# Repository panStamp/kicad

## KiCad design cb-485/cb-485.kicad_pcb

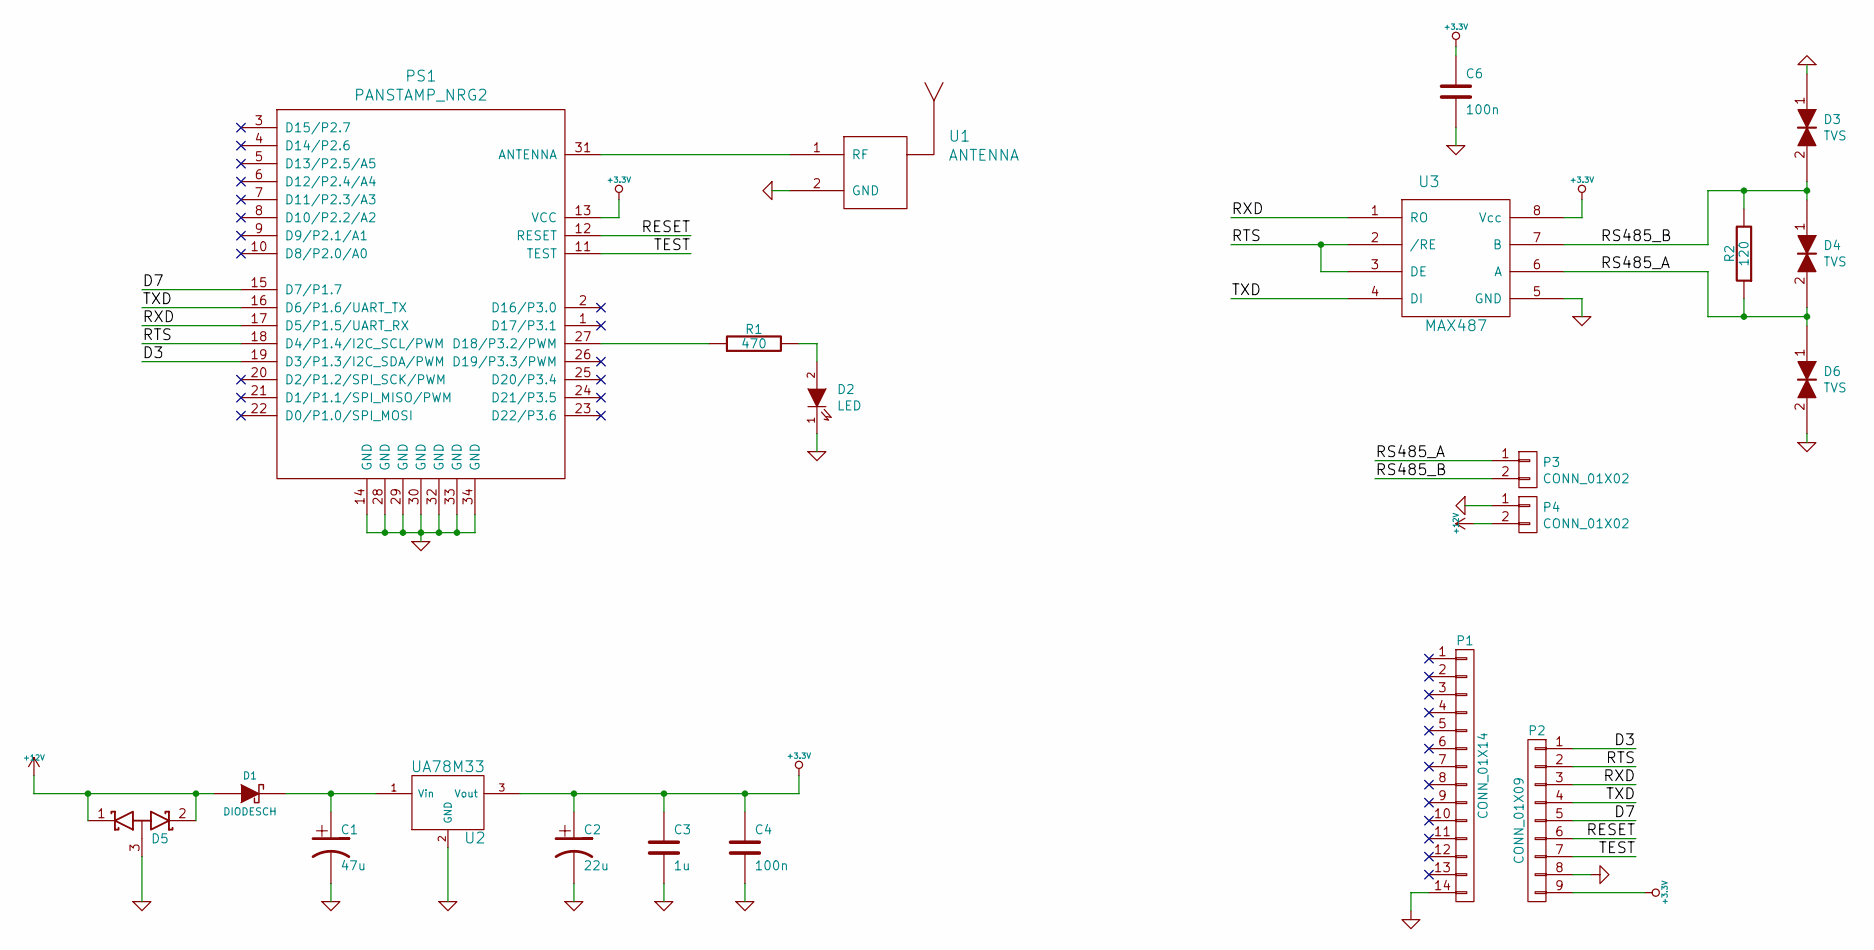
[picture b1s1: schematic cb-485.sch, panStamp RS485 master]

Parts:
C1: 47u; SMDCPOL_6.3
C2: 22u; SMDCPOL_5
C3: 1u; SM0603S
C4, C6: 100n; SM0603S
D1: DIODESCH; SMA
D2: LED; SM0603S_POL
D3, D4, D6: TVS; SOD-923
D5: D_Schottky_x2_ACom_KKA; SOT23
P1: CONN_01X14; Pin_Header_Straight_1x12
P2: CONN_01X09; Pin_Header_Straight_1x09
P3, P4: CONN_01X02; terminal_block_5mm_2P
PS1: PANSTAMP_NRG2; PANSTAMP_2
R1: 470; SM0603S
R2: 120; SM0603S
U1: ANTENNA; SMA_RightAngle_Tyco
U2: UA78M33; SOT223
U3: MAX487; SO8E

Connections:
+3.3V: C2.1, C3.1, C4.1, C6.1, P2.9, PS1.13 (VCC), U2.3 (Vout), U3.8 (Vcc)
+12V: D1.1 (A), D5.1 (K), D5.2 (K), P4.2
/D3: P2.1, PS1.19 (D3/P1.3/I2C_SDA/PWM)
/D7: P2.5, PS1.15 (D7/P1.7)
/RESET: P2.6, PS1.12 (RESET)
/RS485_A: D4.2, D6.1, P3.1, R2.1, U3.6 (A)
/RS485_B: D3.2, D4.1, P3.2, R2.2, U3.7 (B)
/RTS: P2.2, PS1.18 (D4/P1.4/I2C_SCL/PWM), U3.2 (/RE), U3.3 (DE)
/RXD: P2.3, PS1.17 (D5/P1.5/UART_RX), U3.1 (RO)
/TEST: P2.7, PS1.11 (TEST)
/TXD: P2.4, PS1.16 (D6/P1.6/UART_TX), U3.4 (DI)
GND: C1.2, C2.2, C3.2, C4.2, C6.2, D2.1 (K), D3.1, D5.3 (A), D6.2, P1.14, P2.8, P4.1, PS1.14 (GND), PS1.28 (GND), PS1.29 (GND), PS1.30 (GND), PS1.32 (GND), PS1.33 (GND), PS1.34 (GND), U1.2 (GND), U2.2 (GND), U2.4, U3.5 (GND)
unnamed: C1.1, D1.2 (K), U2.1 (Vin)
unnamed: D2.2 (A), R1.2
unnamed: PS1.27 (D18/P3.2/PWM), R1.1
unnamed: PS1.31 (ANTENNA), U1.1 (RF)

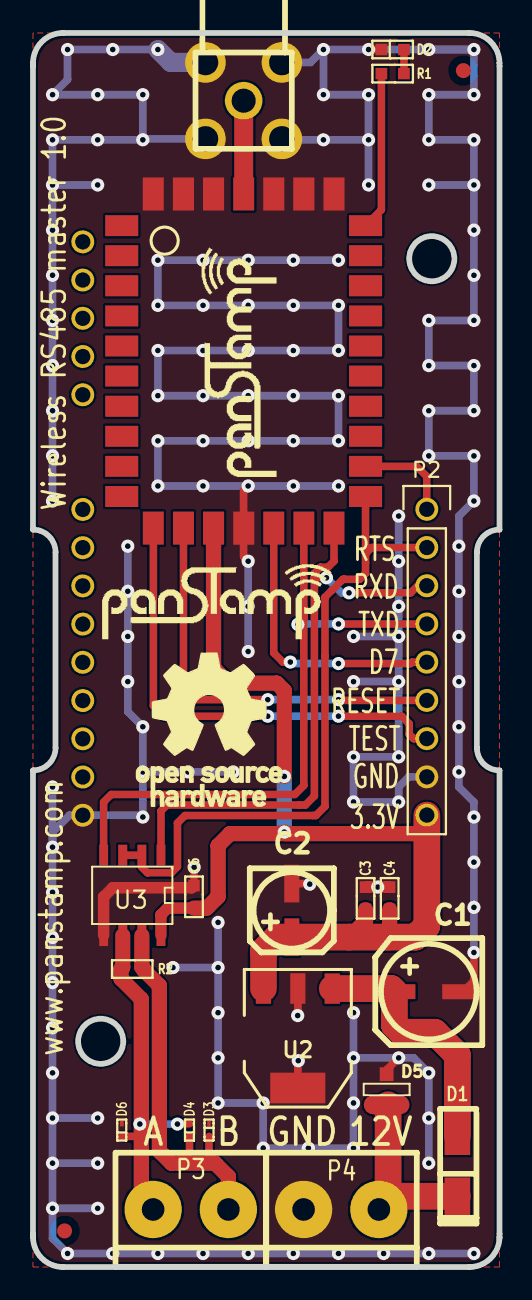
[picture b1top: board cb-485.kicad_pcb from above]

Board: 4 copper layers, 31.0 x 82.0 mm, 23 parts (0 on the bottom side), 16 nets.

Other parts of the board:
fiducial: VAL**; fiducial
fiducial#2: VAL**; fiducial

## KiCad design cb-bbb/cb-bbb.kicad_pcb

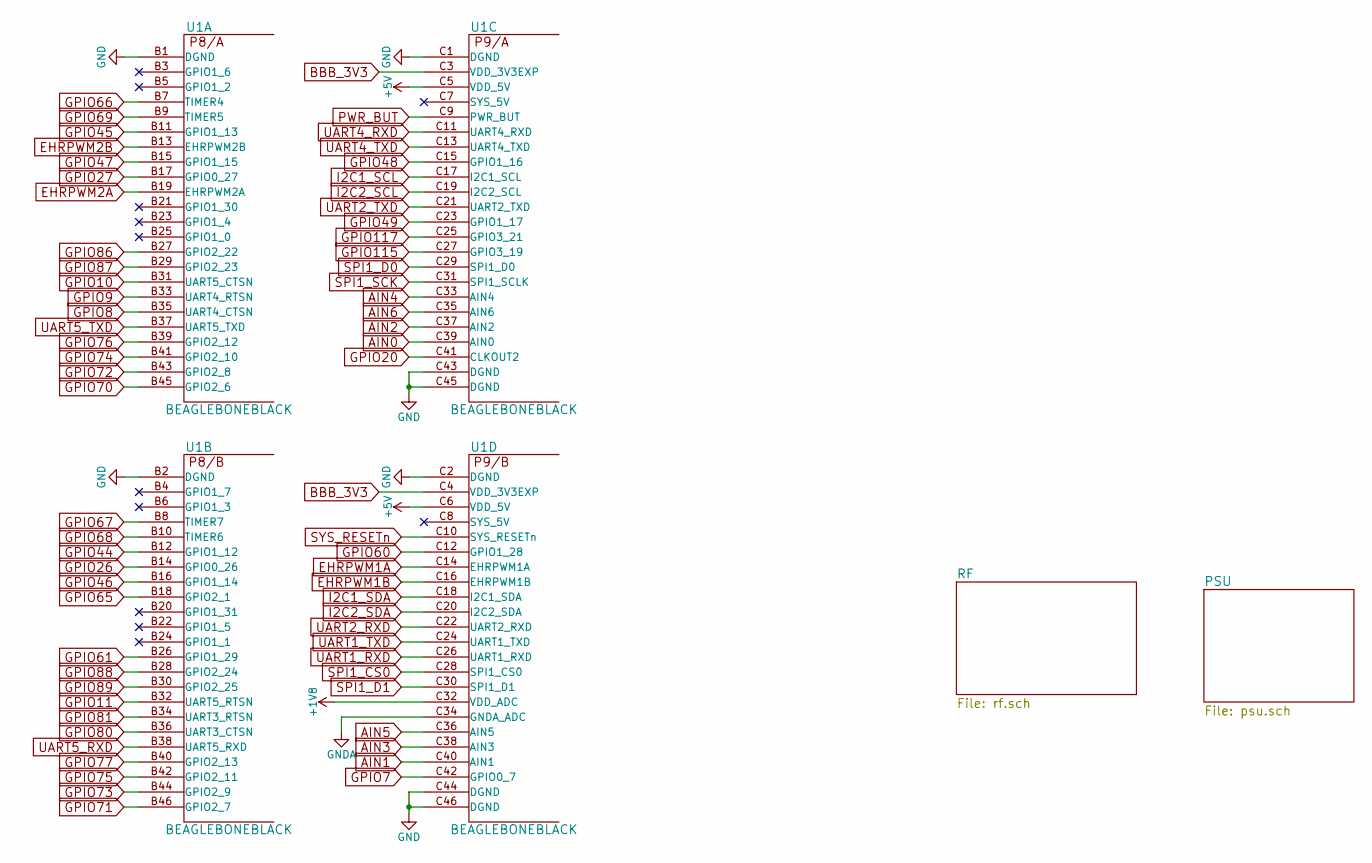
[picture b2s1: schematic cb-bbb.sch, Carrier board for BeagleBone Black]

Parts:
U1: BEAGLEBONEBLACK

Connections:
+1V8: U1.C32 (VDD_ADC)
+5V: U1.C5 (VDD_5V), U1.C6 (VDD_5V); also elsewhere on the board
AIN0: U1.C39 (AIN0)
AIN1: U1.C40 (AIN1)
AIN2: U1.C37 (AIN2)
AIN3: U1.C38 (AIN3)
AIN4: U1.C33 (AIN4)
AIN5: U1.C36 (AIN5)
AIN6: U1.C35 (AIN6)
BBB_3V3: U1.C3 (VDD_3V3EXP), U1.C4 (VDD_3V3EXP); also elsewhere on the board
EHRPWM1A: U1.C14 (EHRPWM1A)
EHRPWM1B: U1.C16 (EHRPWM1B)
EHRPWM2A: U1.B19 (EHRPWM2A)
EHRPWM2B: U1.B13 (EHRPWM2B)
GND: U1.B1 (DGND), U1.B2 (DGND), U1.C1 (DGND), U1.C2 (DGND), U1.C43 (DGND), U1.C44 (DGND), U1.C45 (DGND), U1.C46 (DGND); also elsewhere on the board
GNDA: U1.C34 (GNDA_ADC)
GPIO7: U1.C42 (GPIO0_7); also elsewhere on the board
GPIO8: U1.B35 (UART4_CTSN); also elsewhere on the board
GPIO9: U1.B33 (UART4_RTSN); also elsewhere on the board
GPIO10: U1.B31 (UART5_CTSN)
GPIO11: U1.B32 (UART5_RTSN)
GPIO20: U1.C41 (CLKOUT2); also elsewhere on the board
GPIO26: U1.B14 (GPIO0_26)
GPIO27: U1.B17 (GPIO0_27)
GPIO44: U1.B12 (GPIO1_12)
GPIO45: U1.B11 (GPIO1_13)
GPIO46: U1.B16 (GPIO1_14)
GPIO47: U1.B15 (GPIO1_15)
GPIO48: U1.C15 (GPIO1_16)
GPIO49: U1.C23 (GPIO1_17); also elsewhere on the board
GPIO60: U1.C12 (GPIO1_28); also elsewhere on the board
GPIO61: U1.B26 (GPIO1_29)
GPIO65: U1.B18 (GPIO2_1)
GPIO66: U1.B7 (TIMER4)
GPIO67: U1.B8 (TIMER7)
GPIO68: U1.B10 (TIMER6)
GPIO69: U1.B9 (TIMER5)
GPIO70: U1.B45 (GPIO2_6)
GPIO71: U1.B46 (GPIO2_7)
GPIO72: U1.B43 (GPIO2_8)
GPIO73: U1.B44 (GPIO2_9)
GPIO74: U1.B41 (GPIO2_10)
GPIO75: U1.B42 (GPIO2_11)
GPIO76: U1.B39 (GPIO2_12)
GPIO77: U1.B40 (GPIO2_13)
GPIO80: U1.B36 (UART3_CTSN)
GPIO81: U1.B34 (UART3_RTSN)
GPIO86: U1.B27 (GPIO2_22)
GPIO87: U1.B29 (GPIO2_23)
GPIO88: U1.B28 (GPIO2_24)
GPIO89: U1.B30 (GPIO2_25)
GPIO115: U1.C27 (GPIO3_19); also elsewhere on the board
GPIO117: U1.C25 (GPIO3_21); also elsewhere on the board
I2C1_SCL: U1.C17 (I2C1_SCL)
I2C1_SDA: U1.C18 (I2C1_SDA)
I2C2_SCL: U1.C19 (I2C2_SCL)
I2C2_SDA: U1.C20 (I2C2_SDA)
PWR_BUT: U1.C9 (PWR_BUT)
SPI1_CS0: U1.C28 (SPI1_CS0)
SPI1_D0: U1.C29 (SPI1_D0)
SPI1_D1: U1.C30 (SPI1_D1)
SPI1_SCK: U1.C31 (SPI1_SCLK)
SYS_RESETn: U1.C10 (SYS_RESETn)
UART1_RXD: U1.C26 (UART1_RXD); also elsewhere on the board
UART1_TXD: U1.C24 (UART1_TXD); also elsewhere on the board
UART2_RXD: U1.C22 (UART2_RXD); also elsewhere on the board
UART2_TXD: U1.C21 (UART2_TXD); also elsewhere on the board
UART4_RXD: U1.C11 (UART4_RXD); also elsewhere on the board
UART4_TXD: U1.C13 (UART4_TXD); also elsewhere on the board
UART5_RXD: U1.B38 (UART5_RXD); also elsewhere on the board
UART5_TXD: U1.B37 (UART5_TXD); also elsewhere on the board

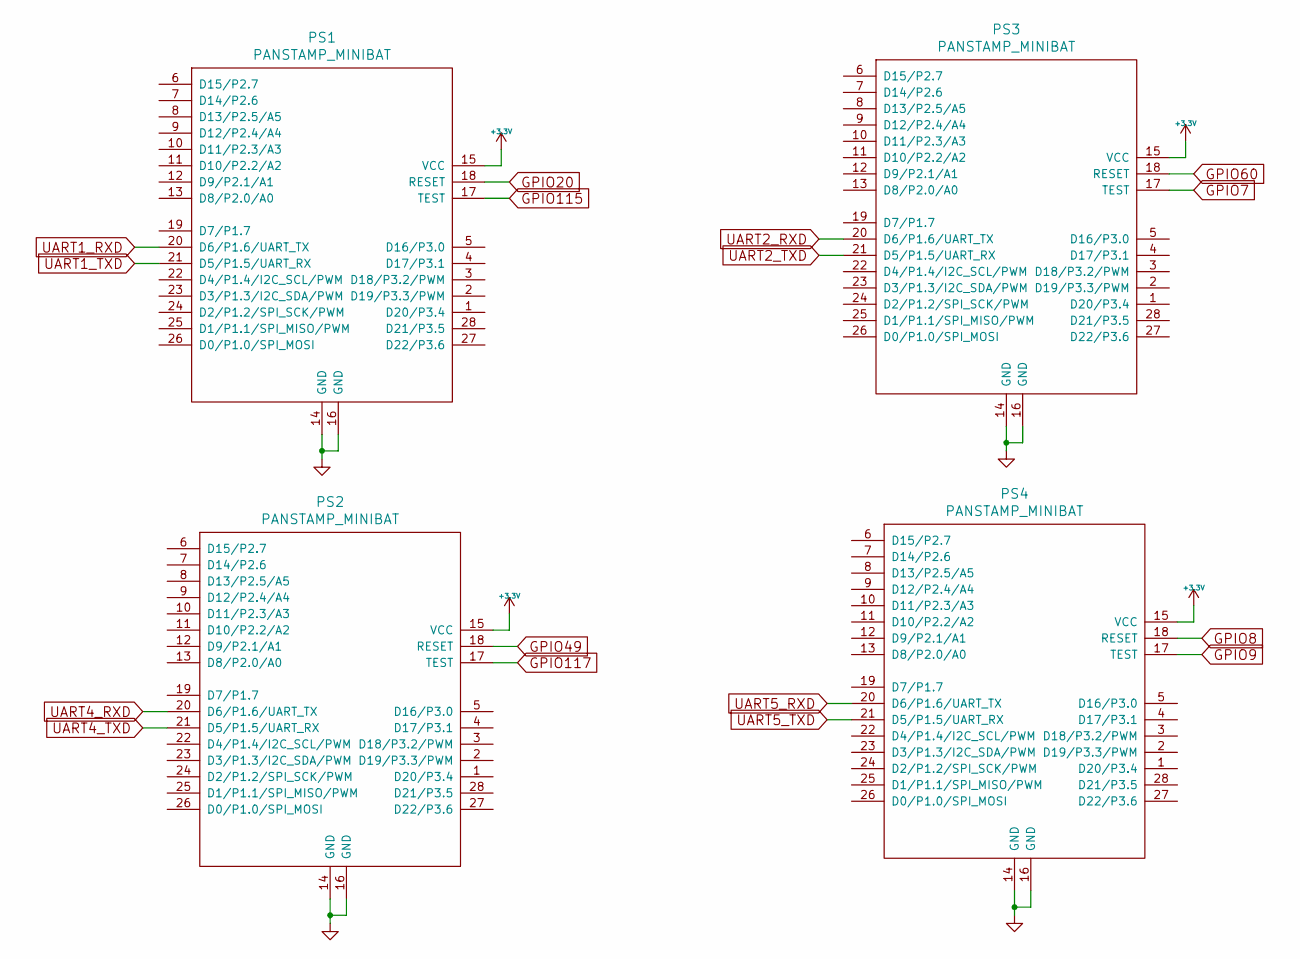
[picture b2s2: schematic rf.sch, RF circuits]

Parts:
PS1, PS2, PS3, PS4: PANSTAMP_MINIBAT; minibat

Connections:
+3V3: PS1.15 (VCC), PS2.15 (VCC), PS3.15 (VCC), PS4.15 (VCC); also elsewhere on the board
GND: PS1.14 (GND), PS1.16 (GND), PS2.14 (GND), PS2.16 (GND), PS3.14 (GND), PS3.16 (GND), PS4.14 (GND), PS4.16 (GND); also elsewhere on the board
GPIO7: PS3.17 (TEST); also elsewhere on the board
GPIO8: PS4.18 (RESET); also elsewhere on the board
GPIO9: PS4.17 (TEST); also elsewhere on the board
GPIO20: PS1.18 (RESET); also elsewhere on the board
GPIO49: PS2.18 (RESET); also elsewhere on the board
GPIO60: PS3.18 (RESET); also elsewhere on the board
GPIO115: PS1.17 (TEST); also elsewhere on the board
GPIO117: PS2.17 (TEST); also elsewhere on the board
UART1_RXD: PS1.20 (D6/P1.6/UART_TX); also elsewhere on the board
UART1_TXD: PS1.21 (D5/P1.5/UART_RX); also elsewhere on the board
UART2_RXD: PS3.20 (D6/P1.6/UART_TX); also elsewhere on the board
UART2_TXD: PS3.21 (D5/P1.5/UART_RX); also elsewhere on the board
UART4_RXD: PS2.20 (D6/P1.6/UART_TX); also elsewhere on the board
UART4_TXD: PS2.21 (D5/P1.5/UART_RX); also elsewhere on the board
UART5_RXD: PS4.20 (D6/P1.6/UART_TX); also elsewhere on the board
UART5_TXD: PS4.21 (D5/P1.5/UART_RX); also elsewhere on the board

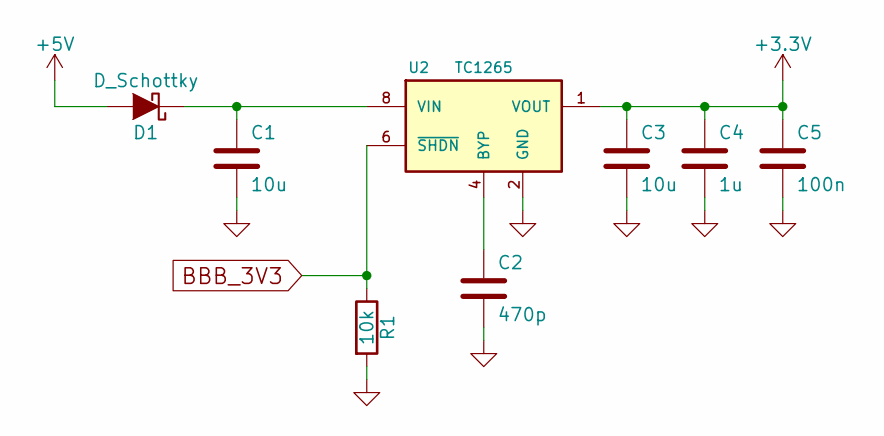
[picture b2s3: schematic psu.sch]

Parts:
C1, C3: 10u; SM0603S
C2: 470p; SM0603S
C4: 1u; SM0603S
C5: 100n; SM0603S
D1: D_Schottky; SMA
R1: 10k; SM0603S
U2: TC1265; SO8E

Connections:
+3V3: C3.1, C4.1, C5.1, U2.1 (VOUT); also elsewhere on the board
+5V: D1.2 (A); also elsewhere on the board
BBB_3V3: R1.1, U2.6 (~SHDN~); also elsewhere on the board
GND: C1.2, C2.2, C3.2, C4.2, C5.2, R1.2, U2.2 (GND); also elsewhere on the board
unnamed: C1.1, D1.1 (K), U2.8 (VIN)
unnamed: C2.1, U2.4 (BYP)

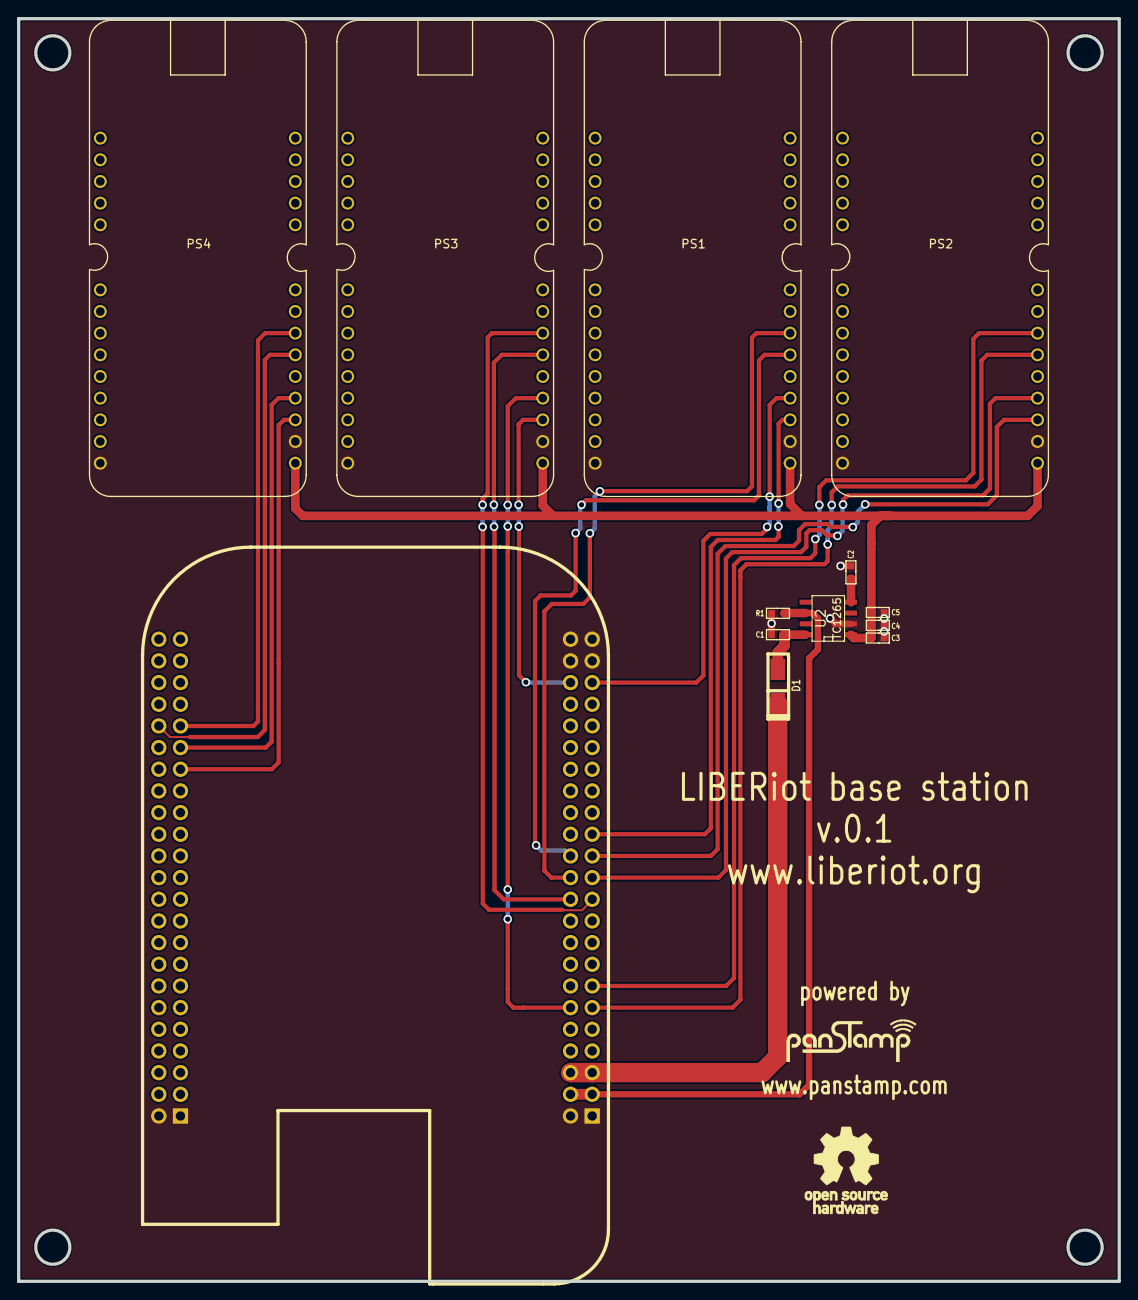
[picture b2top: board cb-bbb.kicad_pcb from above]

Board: 2 copper layers, 129.0 x 148.0 mm, 13 parts (0 on the bottom side), 22 nets.

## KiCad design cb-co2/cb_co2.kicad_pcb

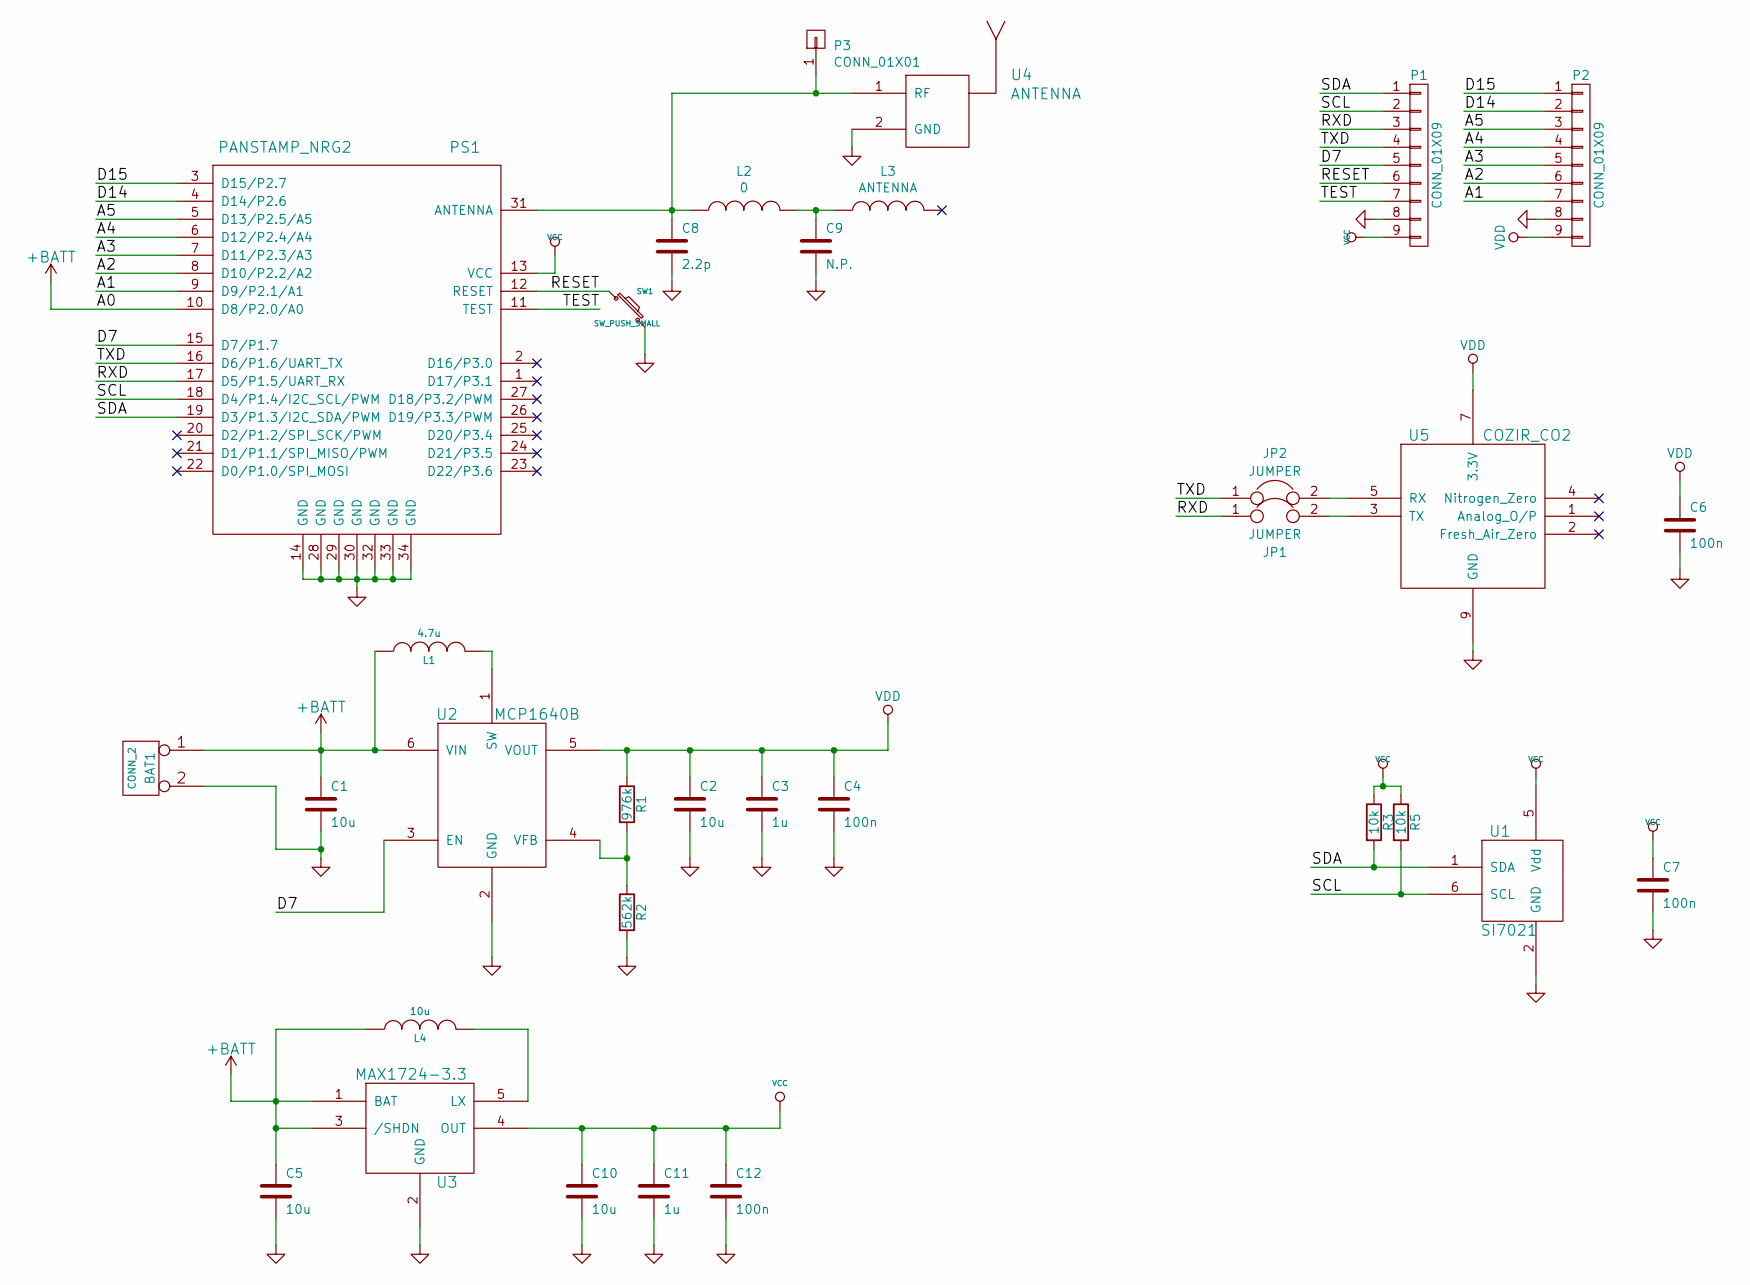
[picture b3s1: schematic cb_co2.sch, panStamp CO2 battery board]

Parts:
BAT1: CONN_2; BAT_AA_HOLDER_02
C1, C2, C5, C10: 10u; SM0603S
C3, C11: 1u; SM0603S
C4, C6, C7, C12: 100n; SM0603S
C8: 2.2p; SM0603S
C9: N.P.; SM0603S
JP1, JP2: JUMPER; Pin_Header_Straight_1x02
L1: 4.7u; R_0805
L2: 0; SM0603S
L3: ANTENNA; 0868AT43A0020
L4: 10u; SM0805
P1, P2: CONN_01X09; Pin_Header_Straight_1x09
P3: CONN_01X01; Pin_Header_Straight_1x01
PS1: PANSTAMP_NRG2; PANSTAMP_2
R1: 976k; SM0603S
R2: 562k; SM0603S
R3, R5: 10k; SM0603S
SW1: SW_PUSH_SMALL; switch-tact-noah
U1: SI7021; DFN-6
U2: MCP1640B; SOT-23-6
U3: MAX1724-3.3; SOT23-5
U4: ANTENNA; U.FL_CONN
U5: COZIR_CO2; COZIR_AS

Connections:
+BATT: BAT1.1, C1.1, C5.1, L1.1, L4.1, PS1.10 (D8/P2.0/A0), U2.6 (VIN), U3.1 (BAT), U3.3 (/SHDN)
/A1: P2.7, PS1.9 (D9/P2.1/A1)
/A2: P2.6, PS1.8 (D10/P2.2/A2)
/A3: P2.5, PS1.7 (D11/P2.3/A3)
/A4: P2.4, PS1.6 (D12/P2.4/A4)
/A5: P2.3, PS1.5 (D13/P2.5/A5)
/D7: P1.5, PS1.15 (D7/P1.7), U2.3 (EN)
/D14: P2.2, PS1.4 (D14/P2.6)
/D15: P2.1, PS1.3 (D15/P2.7)
/RESET: P1.6, PS1.12 (RESET), SW1.1
/RXD: JP1.1, P1.3, PS1.17 (D5/P1.5/UART_RX)
/SCL: P1.2, PS1.18 (D4/P1.4/I2C_SCL/PWM), R5.2, U1.6 (SCL)
/SDA: P1.1, PS1.19 (D3/P1.3/I2C_SDA/PWM), R3.2, U1.1 (SDA)
/TEST: P1.7, PS1.11 (TEST)
/TXD: JP2.1, P1.4, PS1.16 (D6/P1.6/UART_TX)
GND: BAT1.2 (PM), C1.2, C2.2, C3.2, C4.2, C5.2, C6.2, C7.2, C8.2, C9.2, C10.2, C11.2, C12.2, P1.8, P2.8, PS1.14 (GND), PS1.28 (GND), PS1.29 (GND), PS1.30 (GND), PS1.32 (GND), PS1.33 (GND), PS1.34 (GND), R2.2, SW1.2, U1.2 (GND), U2.2 (GND), U3.2 (GND), U4.2 (GND), U5.9 (GND)
unnamed: C8.1, L2.1, P3.1, PS1.31 (ANTENNA), U4.1 (RF)
unnamed: C9.1, L2.2, L3.1
unnamed: JP1.2, U5.3 (TX)
unnamed: JP2.2, U5.5 (RX)
unnamed: L1.2, U2.1 (SW)
unnamed: L4.2, U3.5 (LX)
unnamed: R1.2, R2.1, U2.4 (VFB)
VCC: C7.1, C10.1, C11.1, C12.1, P1.9, PS1.13 (VCC), R3.1, R5.1, U1.5 (Vdd), U3.4 (OUT)
VDD: C2.1, C3.1, C4.1, C6.1, P2.9, R1.1, U2.5 (VOUT), U5.7 (3.3V)

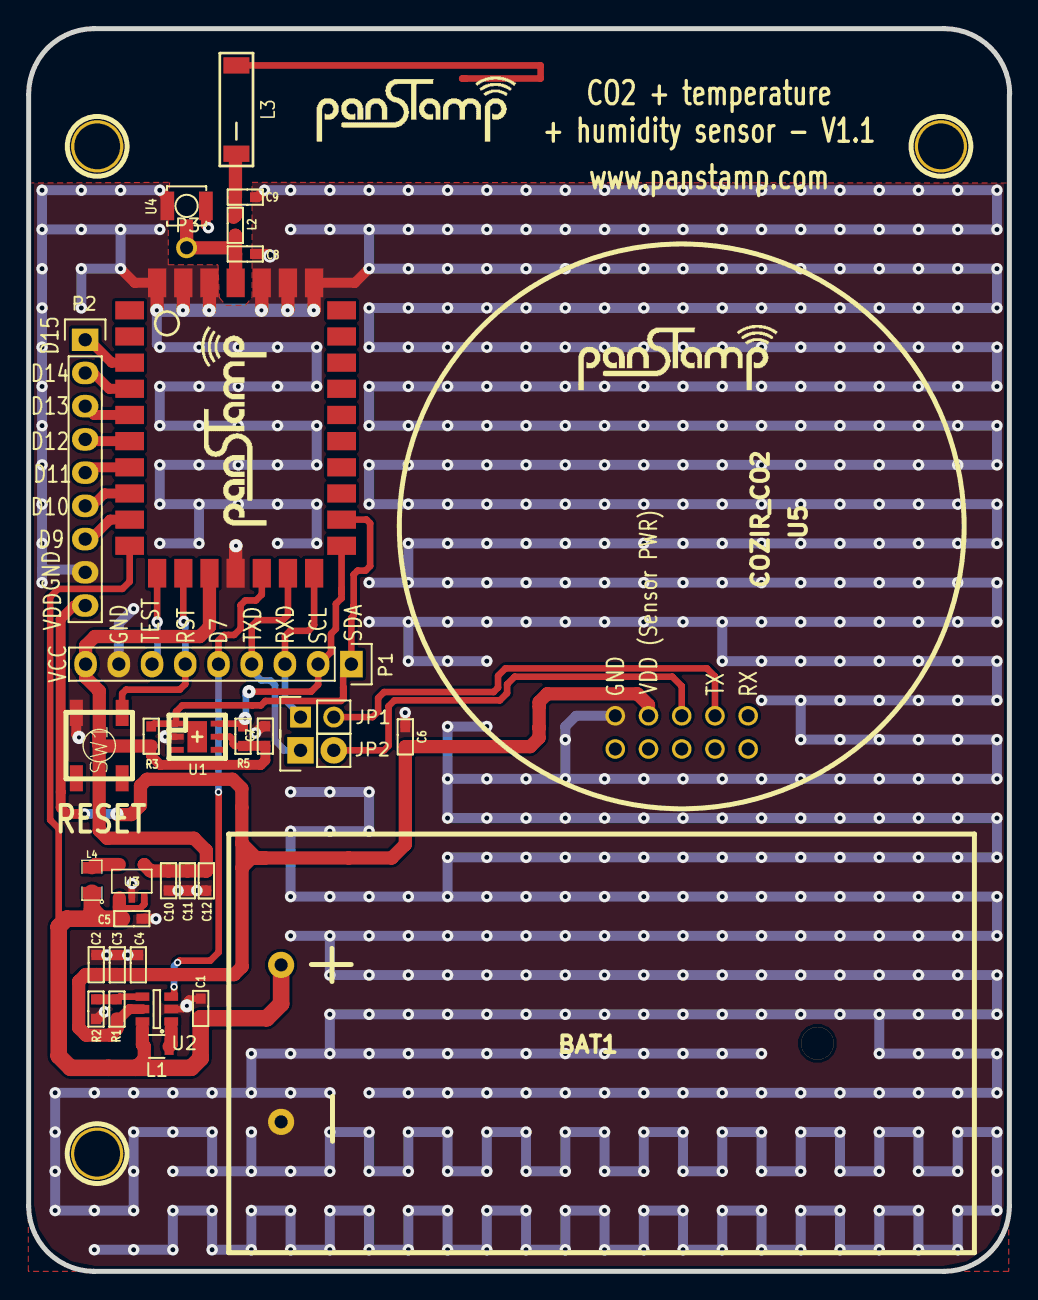
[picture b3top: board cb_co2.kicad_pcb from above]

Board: 4 copper layers, 75.0 x 95.0 mm, 38 parts (0 on the bottom side), 25 nets.

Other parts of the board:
1PIN, 1PIN#2, 1PIN#3: P***; 1pin
www.panstamp.com: PANSTAMPLOGO
www.panstamp.com#2: Battery board V.2.0; PANSTAMPLOGO

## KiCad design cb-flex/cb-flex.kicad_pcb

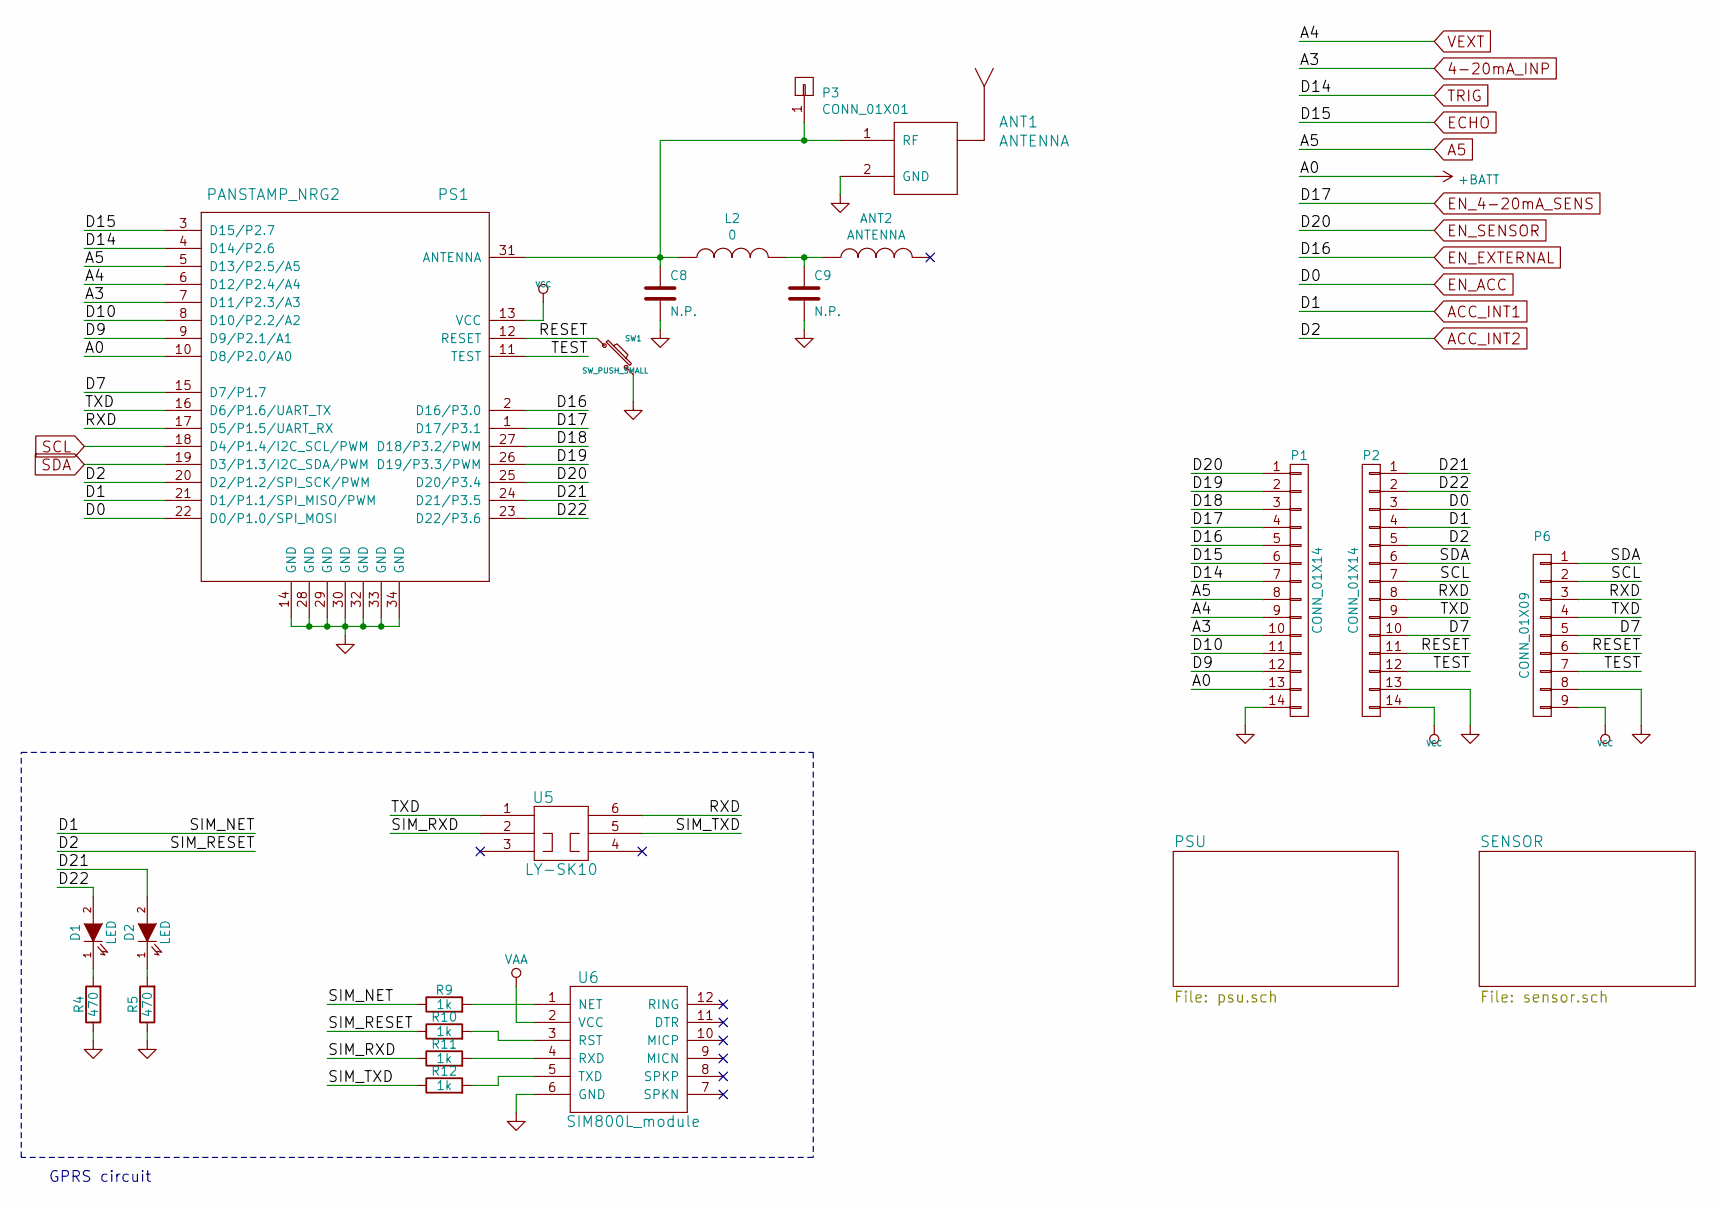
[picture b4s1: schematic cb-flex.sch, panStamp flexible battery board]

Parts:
ANT1: ANTENNA; U.FL_CONN
ANT2: ANTENNA; 0868AT43A0020
C8, C9: N.P.; SM0603S
D1, D2: LED; SM0603S_POL
L2: 0; SM0603S
P1, P2: CONN_01X14; Pin_Header_Straight_1x12
P3: CONN_01X01; Pin_Header_Straight_1x01
P6: CONN_01X09; Pin_Header_Straight_1x09
PS1: PANSTAMP_NRG2; PANSTAMP_2
R4, R5: 470; SM0603S
R9, R10, R11, R12: 1k; SM0603S
SW1: SW_PUSH_SMALL; switch-tact-noah
U5: LY-SK10
U6: SIM800L_module; SIM800L_MODULE

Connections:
4-20mA_INP: P1.10, PS1.7 (D11/P2.3/A3); also elsewhere on the board
+BATT: P1.13, PS1.10 (D8/P2.0/A0); also elsewhere on the board
/D7: P2.10, P6.5, PS1.15 (D7/P1.7)
/D9: P1.12, PS1.9 (D9/P2.1/A1)
/D10: P1.11, PS1.8 (D10/P2.2/A2)
/D18: P1.3, PS1.27 (D18/P3.2/PWM)
/D19: P1.2, PS1.26 (D19/P3.3/PWM)
/D21: D2.2 (A), P2.1, PS1.24 (D21/P3.5)
/D22: D1.2 (A), P2.2, PS1.23 (D22/P3.6)
/RESET: P2.11, P6.6, PS1.12 (RESET), SW1.1
/RXD: P2.8, P6.3, PS1.17 (D5/P1.5/UART_RX), U5.6
/SIM_RXD: R11.1, U5.2
/SIM_TXD: R12.1, U5.5
/TEST: P2.12, P6.7, PS1.11 (TEST)
/TXD: P2.9, P6.4, PS1.16 (D6/P1.6/UART_TX), U5.1
A5: P1.8, PS1.5 (D13/P2.5/A5); also elsewhere on the board
ACC_INT1: P2.4, PS1.21 (D1/P1.1/SPI_MISO/PWM), R9.1; also elsewhere on the board
ACC_INT2: P2.5, PS1.20 (D2/P1.2/SPI_SCK/PWM), R10.1; also elsewhere on the board
ECHO: P1.6, PS1.3 (D15/P2.7); also elsewhere on the board
EN_4-20mA_SENS: P1.4, PS1.1 (D17/P3.1); also elsewhere on the board
EN_ACC: P2.3, PS1.22 (D0/P1.0/SPI_MOSI); also elsewhere on the board
EN_EXTERNAL: P1.5, PS1.2 (D16/P3.0); also elsewhere on the board
EN_SENSOR: P1.1, PS1.25 (D20/P3.4); also elsewhere on the board
GND: ANT1.2 (GND), C8.2, C9.2, P1.14, P2.13, P6.8, PS1.14 (GND), PS1.28 (GND), PS1.29 (GND), PS1.30 (GND), PS1.32 (GND), PS1.33 (GND), PS1.34 (GND), R4.1, R5.1, SW1.2, U6.6 (GND); also elsewhere on the board
unnamed: ANT1.1 (RF), C8.1, L2.1, P3.1, PS1.31 (ANTENNA)
unnamed: ANT2.1, C9.1, L2.2
unnamed: D1.1 (K), R4.2
unnamed: D2.1 (K), R5.2
unnamed: R9.2, U6.1 (NET)
unnamed: R10.2, U6.3 (RST)
unnamed: R11.2, U6.4 (RXD)
unnamed: R12.2, U6.5 (TXD)
SCL: P2.7, P6.2, PS1.18 (D4/P1.4/I2C_SCL/PWM); also elsewhere on the board
SDA: P2.6, P6.1, PS1.19 (D3/P1.3/I2C_SDA/PWM); also elsewhere on the board
TRIG: P1.7, PS1.4 (D14/P2.6); also elsewhere on the board
VAA: U6.2 (VCC); also elsewhere on the board
VCC: P2.14, P6.9, PS1.13 (VCC); also elsewhere on the board
VEXT: P1.9, PS1.6 (D12/P2.4/A4); also elsewhere on the board

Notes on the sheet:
GPRS circuit

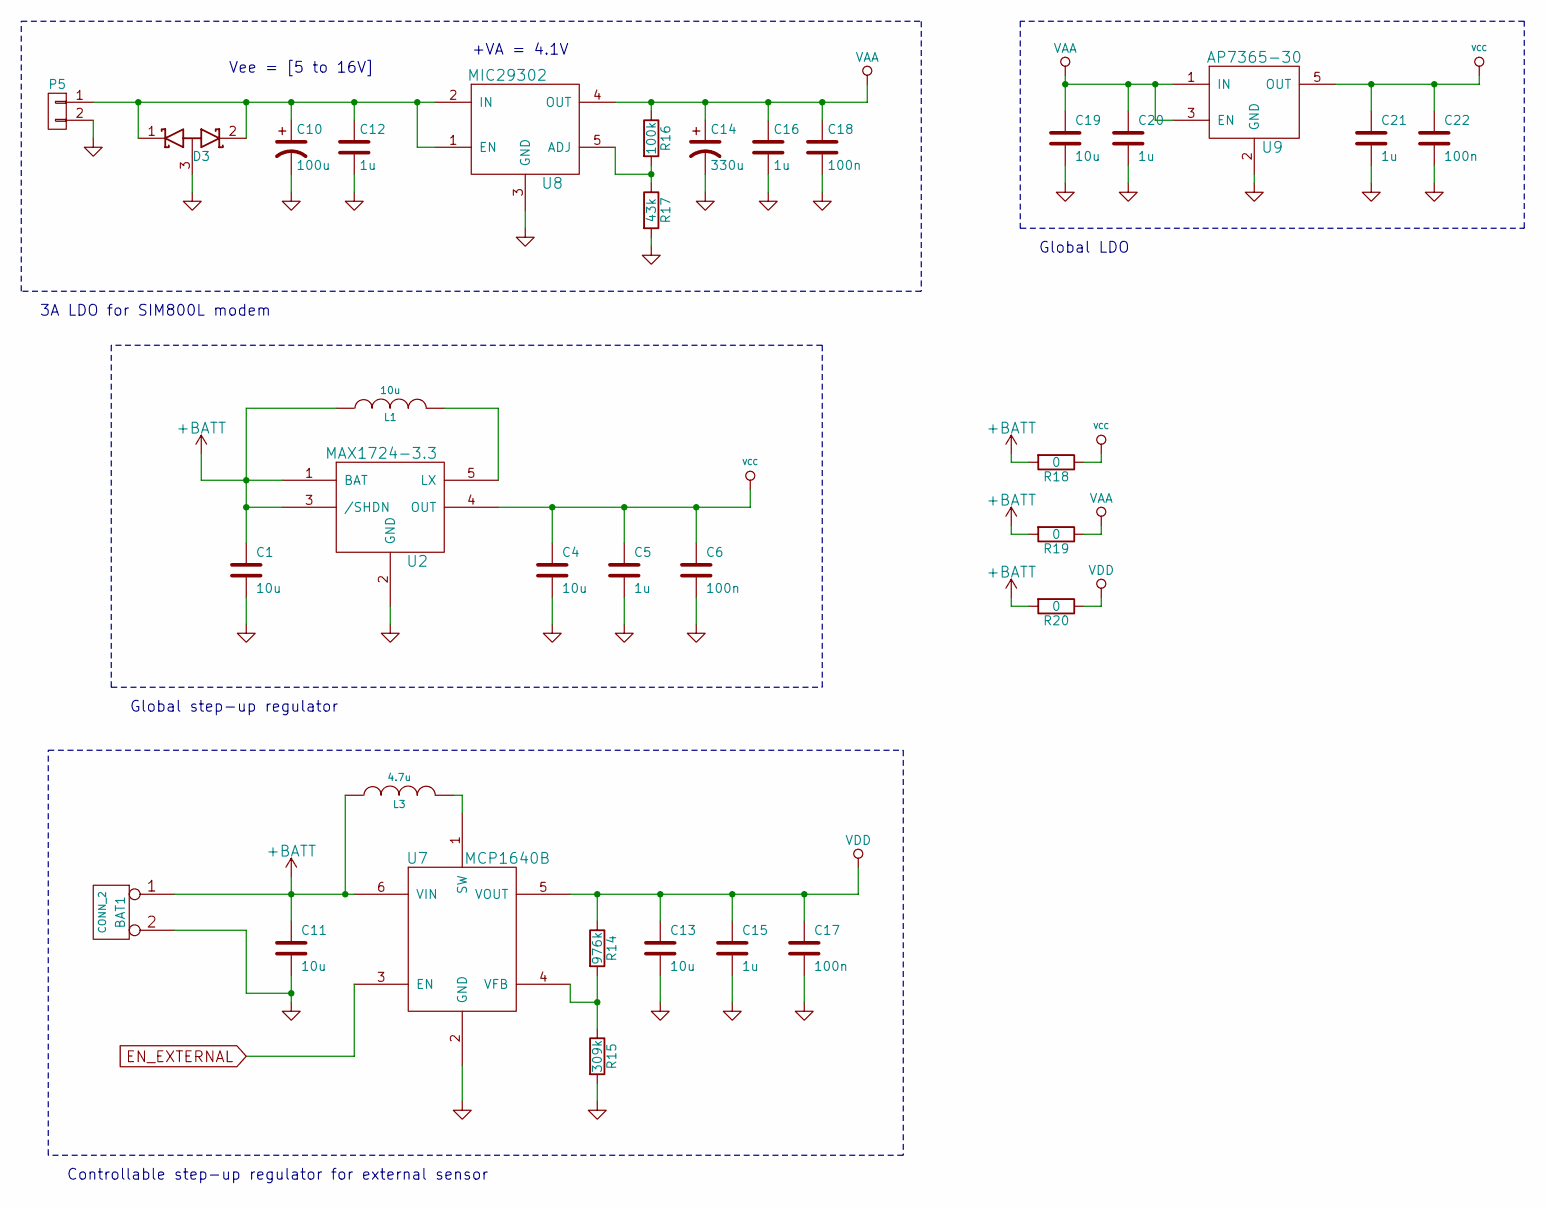
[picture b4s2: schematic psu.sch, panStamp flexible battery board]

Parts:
BAT1: CONN_2; BAT_AA_HOLDER_02
C1, C4, C11, C13, C19: 10u; SM0603S
C5, C12, C15, C16, C20, C21: 1u; SM0603S
C6, C17, C18, C22: 100n; SM0603S
C10: 100u; SMDCPOL_6.3
C14: 330u; SMDCPOL_8
D3: D_Schottky_x2_ACom_KKA; SOT23
L1: 10u; SM0805
L3: 4.7u; SM0805
P5: CONN_01X02; terminal_block_5mm_2P
R14: 976k; SM0603S
R15: 309k; SM0603S
R16: 100k; SM0603S
R17: 43k; SM0603S
R18, R19, R20: 0; SM0603S
U2: MAX1724-3.3; SOT23-5
U7: MCP1640B; SOT23_6
U8: MIC29302; TO-252
U9: AP7365-30; SOT23-5

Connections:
+BATT: BAT1.1, C1.1, C11.1, L1.1, L3.1, R18.2, R19.2, R20.2, U2.1 (BAT), U2.3 (/SHDN), U7.6 (VIN); also elsewhere on the board
EN_EXTERNAL: U7.3 (EN); also elsewhere on the board
GND: BAT1.2 (PM), C1.2, C4.2, C5.2, C6.2, C10.2, C11.2, C12.2, C13.2, C14.2, C15.2, C16.2, C17.2, C18.2, C19.2, C20.2, C21.2, C22.2, D3.3 (A), P5.2, R15.2, R17.2, U2.2 (GND), U7.2 (GND), U8.3 (GND), U9.2 (GND); also elsewhere on the board
unnamed: C10.1, C12.1, D3.1 (K), D3.2 (K), P5.1, U8.1 (EN), U8.2 (IN)
unnamed: L1.2, U2.5 (LX)
unnamed: L3.2, U7.1 (SW)
unnamed: R14.2, R15.1, U7.4 (VFB)
unnamed: R16.2, R17.1, U8.5 (ADJ)
VAA: C14.1, C16.1, C18.1, C19.1, C20.1, R16.1, R19.1, U8.4 (OUT), U9.1 (IN), U9.3 (EN); also elsewhere on the board
VCC: C4.1, C5.1, C6.1, C21.1, C22.1, R18.1, U2.4 (OUT), U9.5 (OUT); also elsewhere on the board
VDD: C13.1, C15.1, C17.1, R14.1, R20.1, U7.5 (VOUT); also elsewhere on the board

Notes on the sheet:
+VA = 4.1V
Vee = [5 to 16V]
Controllable step-up regulator for external sensor
Global step-up regulator
3A LDO for SIM800L modem
Global LDO
